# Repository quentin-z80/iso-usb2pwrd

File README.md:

# iso-usb2pwrd

USB-C 2.0 Isolator with 1W Power passthrough

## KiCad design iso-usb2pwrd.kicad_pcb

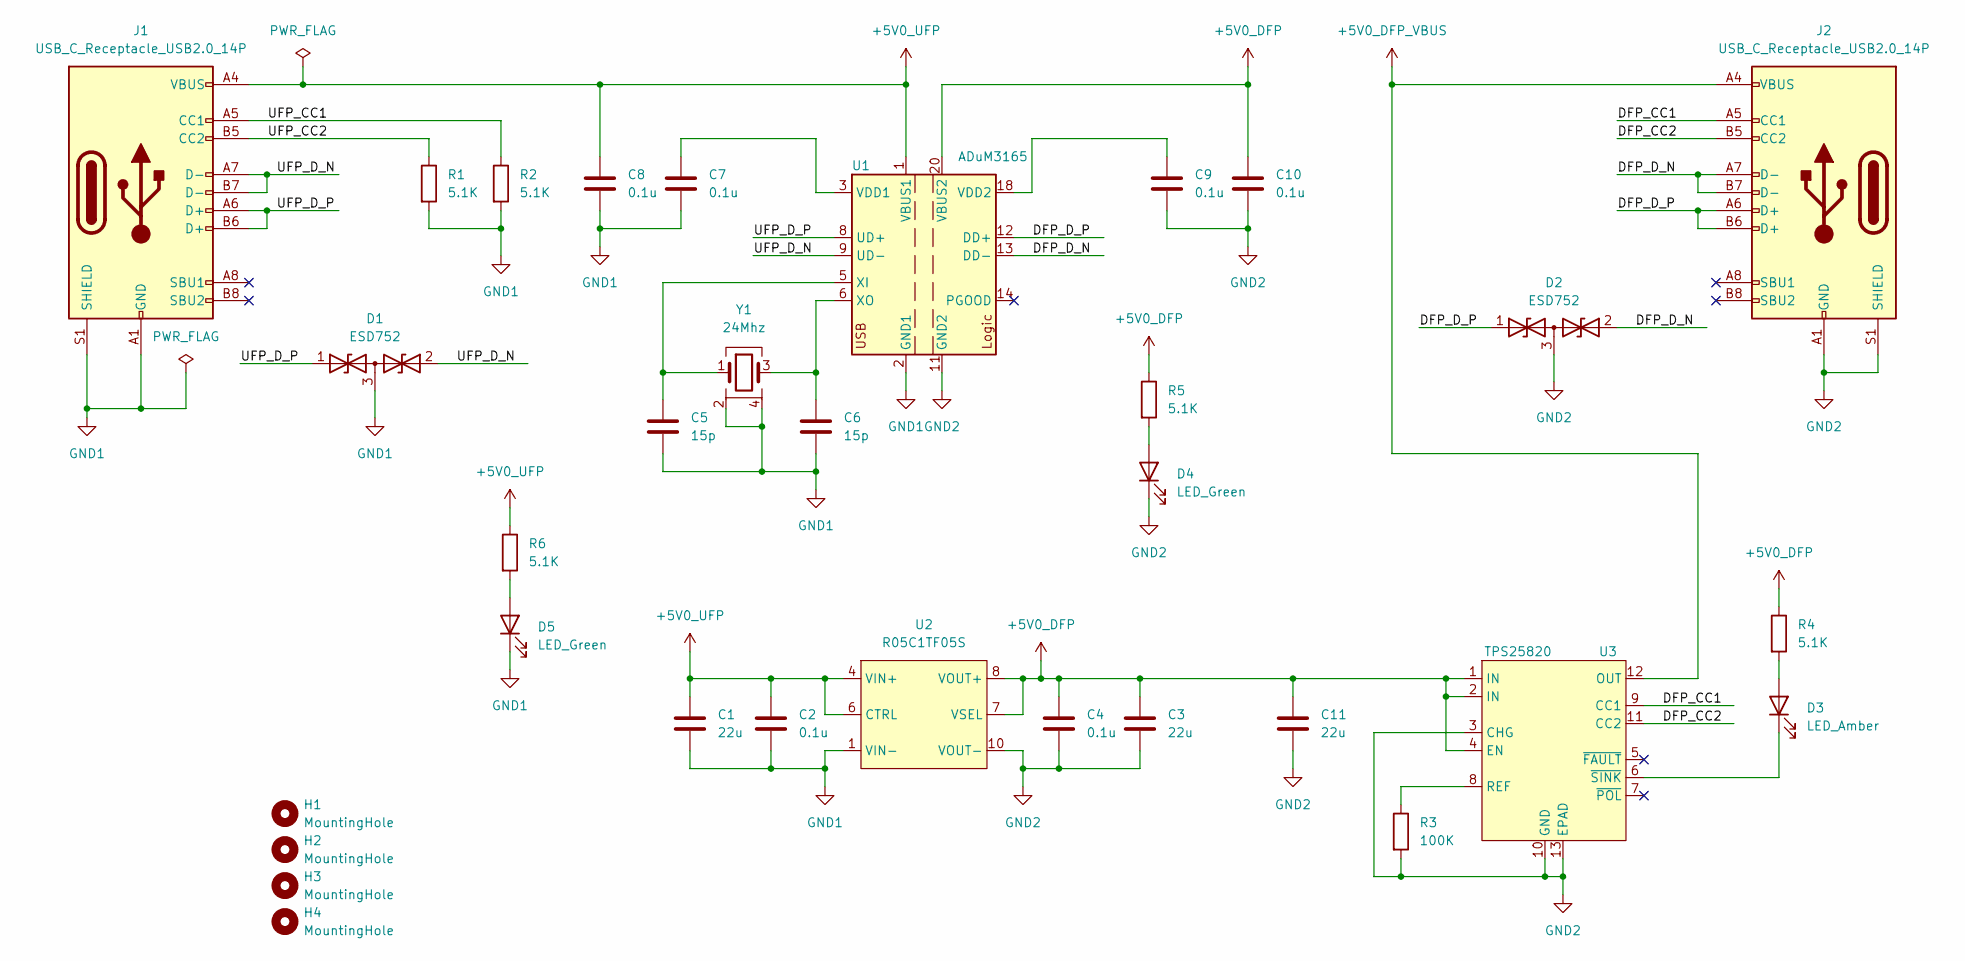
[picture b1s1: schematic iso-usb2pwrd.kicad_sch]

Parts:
C1, C3, C11: 22u; C_1210_3225Metric; MPN CL32B226MOJNNNE
C2, C4, C7, C8, C9, C10: 0.1u; C_0402_1005Metric; MPN GCM155R71H104KE02D
C5, C6: 15p; C_0402_1005Metric; MPN 0402N150J250CT
D1, D2: ESD752; SOT-323_SC-70; MPN ESD752DCKR
D3: LED_Amber; LED_0603_1608Metric; MPN SML-D12D1WT86
D4, D5: LED_Green; LED_0603_1608Metric; MPN SML-D12M8WT86
H1, H2, H3, H4: MountingHole; MountingHole_2.2mm_M2
J1, J2: USB_C_Receptacle_USB2.0_14P; USB_C_Receptacle_GCT_USB4105-xx-A_16P_TopMnt_Horizontal; MPN USB4105-GF-A
R1, R2, R4, R5, R6: 5.1K; R_0402_1005Metric; MPN RC0402FR-075K1L
R3: 100K; R_0402_1005Metric; MPN RC0402FR-07100KL
U1: ADuM3165; SSOP-20_5.3x7.2mm_P0.65mm; MPN ADUM3165BRSZ-RL
U2: R05C1TF05S; Package_LGA-12_5x4mm; MPN R05C1TF05S-R
U3: TPS25820; WSON-12-1EP_3x2mm_P0.5mm_EP1x2.65_ThermalVias; MPN TPS25820DSSR
Y1: 24Mhz; Crystal_SMD_2016-4Pin_2.0x1.6mm; MPN ECS-240-12-37B-CKY-TR

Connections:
+5V0_DFP: C3.1, C4.1, C10.1, C11.1, R4.1, R5.1, U1.20 (VBUS2), U2.7 (VSEL), U2.8 (VOUT+), U2.9 (VOUT+), U3.1 (IN), U3.2 (IN), U3.4 (EN)
+5V0_DFP_VBUS: J2.A4 (VBUS), J2.A9 (VBUS), J2.B4 (VBUS), J2.B9 (VBUS), U3.12 (OUT)
+5V0_UFP: C1.1, C2.1, C8.1, J1.A4 (VBUS), J1.A9 (VBUS), J1.B4 (VBUS), J1.B9 (VBUS), R6.1, U1.1 (VBUS1), U2.4 (VIN+), U2.5 (VIN+), U2.6 (CTRL)
/DFP_CC1: J2.A5 (CC1), U3.9 (CC1)
/DFP_CC2: J2.B5 (CC2), U3.11 (CC2)
/DFP_D_N: D2.2 (A2), J2.A7 (D-), J2.B7 (D-), U1.13 (DD-)
/DFP_D_P: D2.1 (A1), J2.A6 (D+), J2.B6 (D+), U1.12 (DD+)
/UFP_CC1: J1.A5 (CC1), R2.1
/UFP_CC2: J1.B5 (CC2), R1.1
/UFP_D_N: D1.2 (A2), J1.A7 (D-), J1.B7 (D-), U1.9 (UD-)
/UFP_D_P: D1.1 (A1), J1.A6 (D+), J1.B6 (D+), U1.8 (UD+)
GND1: C1.2, C2.2, C5.2, C6.2, C7.2, C8.2, D1.3 (common), D5.1 (K), J1.A1 (GND), J1.A12 (GND), J1.B1 (GND), J1.B12 (GND), J1.S1 (SHIELD), R1.2, R2.2, U1.2 (GND1), U1.4 (GND1), U1.7 (GND1), U1.10 (GND1), U2.1 (VIN-), U2.2 (VIN-), U2.3 (VIN-), Y1.2, Y1.4
GND2: C3.2, C4.2, C9.2, C10.2, C11.2, D2.3 (common), D4.1 (K), J2.A1 (GND), J2.A12 (GND), J2.B1 (GND), J2.B12 (GND), J2.S1 (SHIELD), R3.2, U1.11 (GND2), U1.15 (GND2), U1.16 (GND2), U1.17 (GND2), U1.19 (GND2), U2.10 (VOUT-), U2.11 (VOUT-), U2.12 (VOUT-), U3.3 (CHG), U3.10 (GND), U3.13 (EPAD)
unnamed: D3.2 (A), R4.2
unnamed: D3.1 (K), U3.6 (~SINK)
unnamed: D4.2 (A), R5.2
unnamed: D5.2 (A), R6.2
unnamed: C7.1, U1.3 (VDD1)
unnamed: C9.1, U1.18 (VDD2)
unnamed: C5.1, U1.5 (XI), Y1.1
unnamed: C6.1, U1.6 (XO), Y1.3
unnamed: R3.1, U3.8 (REF)

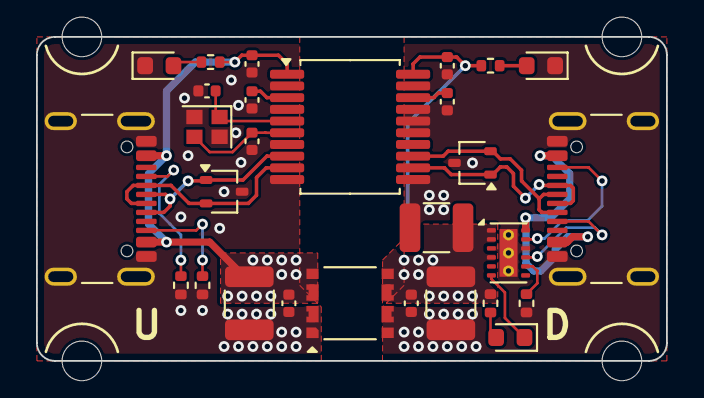
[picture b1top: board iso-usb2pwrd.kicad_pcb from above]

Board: 2 copper layers, 35.0 x 18.0 mm, 32 parts (0 on the bottom side), 22 nets.

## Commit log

2024-07-22 inital commit
2024-07-22 update panel config: reduce vspace
2024-07-22 add board rev
2024-07-22 update libs
2024-08-09 add readme
2024-08-09 add images of board
2024-08-09 add pdf sch
